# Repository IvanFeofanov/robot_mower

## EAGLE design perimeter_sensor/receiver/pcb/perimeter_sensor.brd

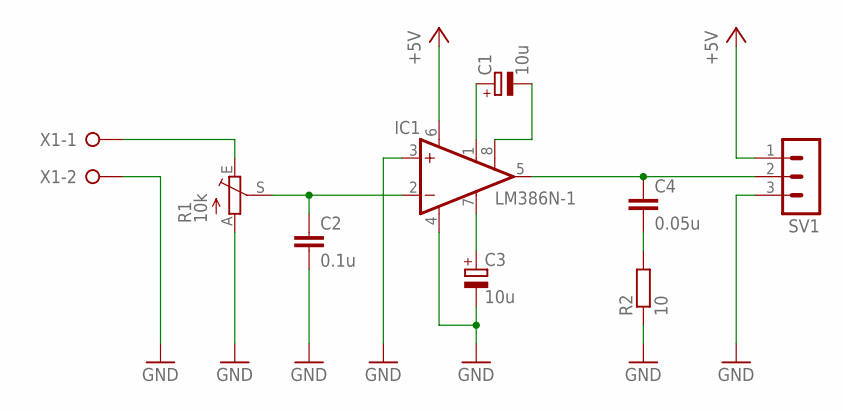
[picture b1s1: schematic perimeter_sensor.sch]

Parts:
C1, C3: 10u; E2,5-6
C2: 0.1u; C050-025X075
C4: 0.05u; C050-025X075
IC1: LM386N-1; DIL08
R1: 10k; S64W
R2: 10; 0204/7
SV1: MA03-1
X1: W237-02P; W237-132

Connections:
+5V: IC1.6 (VS), SV1.1
GND: C2.2, C3.-, IC1.3 (+IN), IC1.4 (GND), R1.A, R2.1, SV1.3, X1.2
unnamed: C1.-, IC1.8 (GAIN)
unnamed: C1.+, IC1.1 (GAIN)
unnamed: C3.+, IC1.7 (BYPASS)
unnamed: C2.1, IC1.2 (-IN), R1.S
unnamed: C4.1, IC1.5 (OUT), SV1.2
unnamed: C4.2, R2.2
unnamed: R1.E, X1.1

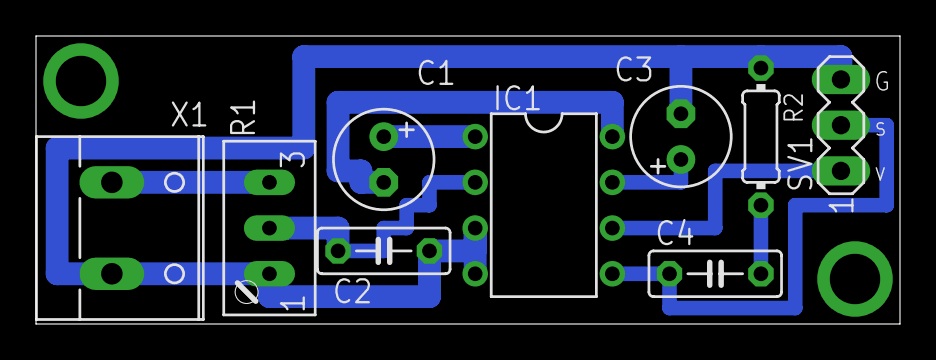
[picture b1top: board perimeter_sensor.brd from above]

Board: 2 copper layers, 48.0 x 16.0 mm, 9 parts (0 on the bottom side), 9 nets.

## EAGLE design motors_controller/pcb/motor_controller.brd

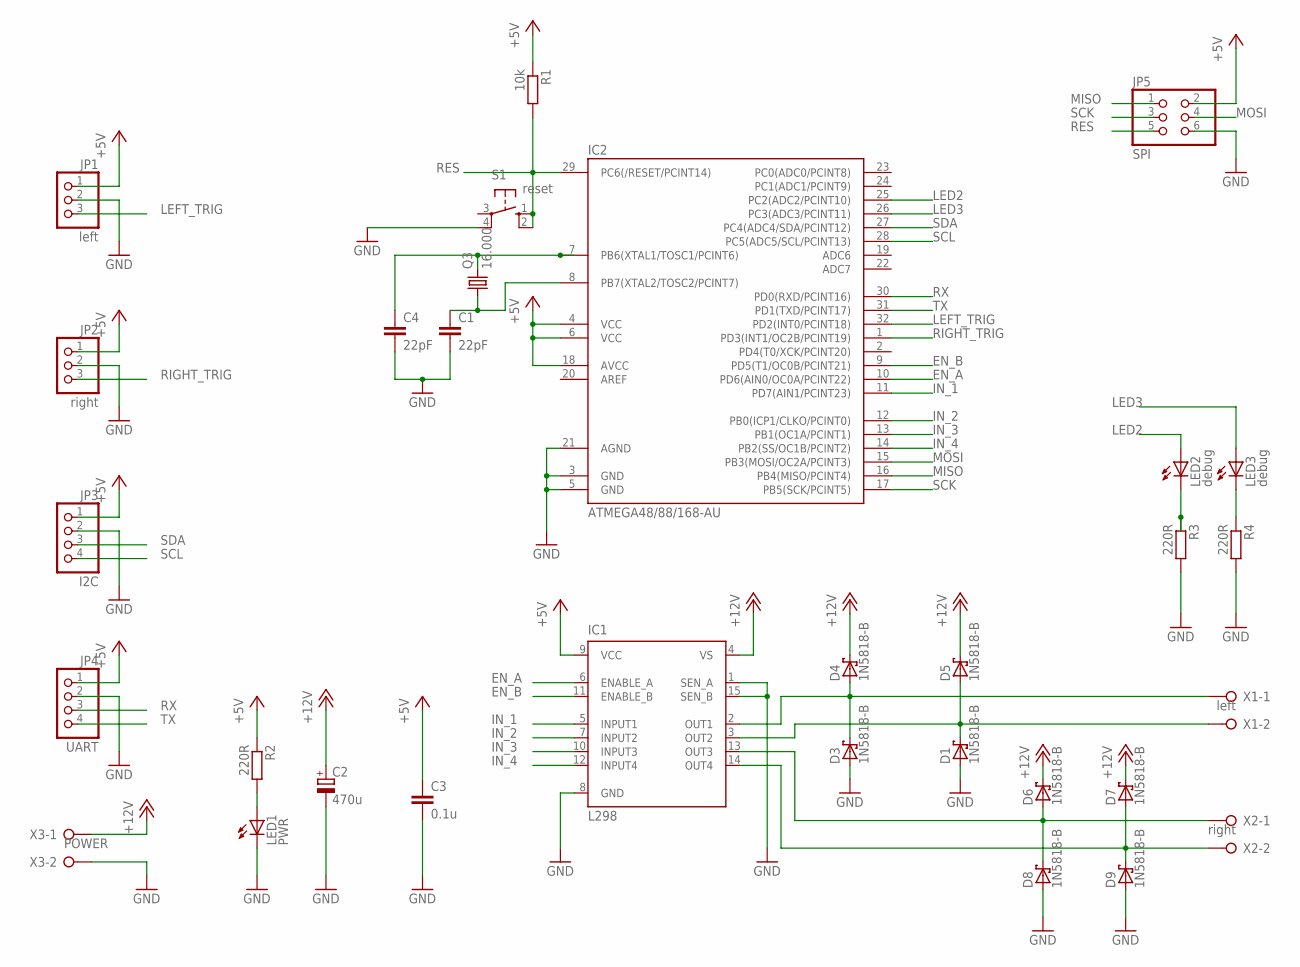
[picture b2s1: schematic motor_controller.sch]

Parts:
C1, C4: 22pF; C0805
C2: 470u; E5-10,5
C3: 0.1u; C0805
D1, D3, D4, D5, D6, D7, D8, D9: 1N5818-B; DO41-7.6
IC1: L298; MULTIWATT-15
IC2: ATMEGA48/88/168-AU; TQFP32-08
JP1: left; 1X03
JP2: right; 1X03
JP3: I2C; 1X04
JP4: UART; 1X04
JP5: SPI; 2X03
LED1: PWR; LED_1206
LED2, LED3: debug; LED_1206
Q3: 16.000; HC49UP
R1: 10k; R0805
R2, R3, R4: 220R; R0805
S1: reset; B3F-10XX
X1: left; W237-132
X2: right; W237-132
X3: POWER; W237-132

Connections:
+5V: C3.1, IC1.9 (VCC), IC2.4 (VCC), IC2.6 (VCC), IC2.18 (AVCC), JP1.1, JP2.1, JP3.1, JP4.1, JP5.2, R1.1, R2.1
+12V: C2.+, D4.C, D5.C, D6.C, D7.C, IC1.4 (VS), X3.1
EN_A: IC1.6 (ENABLE_A), IC2.10 (PD6(AIN0/OC0A/PCINT22))
EN_B: IC1.11 (ENABLE_B), IC2.9 (PD5(T1/OC0B/PCINT21))
GND: C1.2, C2.-, C3.2, C4.2, D1.A, D3.A, D8.A, D9.A, IC1.1 (SEN_A), IC1.8 (GND), IC1.15 (SEN_B), IC2.3 (GND), IC2.5 (GND), IC2.21 (AGND), JP1.2, JP2.2, JP3.2, JP4.2, JP5.6, LED1.C, R3.2, R4.2, S1.4 (P1), X3.2
IN_1: IC1.5 (INPUT1), IC2.11 (PD7(AIN1/PCINT23))
IN_2: IC1.7 (INPUT2), IC2.12 (PB0(ICP1/CLKO/PCINT0))
IN_3: IC1.10 (INPUT3), IC2.13 (PB1(OC1A/PCINT1))
IN_4: IC1.12 (INPUT4), IC2.14 (PB2(SS/OC1B/PCINT2))
LED2: IC2.25 (PC2(ADC2/PCINT10)), LED2.A
LED3: IC2.26 (PC3(ADC3/PCINT11)), LED3.A
LEFT_TRIG: IC2.32 (PD2(INT0/PCINT18)), JP1.3
MISO: IC2.16 (PB4(MISO/PCINT4)), JP5.1
MOSI: IC2.15 (PB3(MOSI/OC2A/PCINT3)), JP5.4
unnamed: LED1.A, R2.2
unnamed: C4.1, IC2.7 (PB6(XTAL1/TOSC1/PCINT6)), Q3.2
unnamed: C1.1, IC2.8 (PB7(XTAL2/TOSC2/PCINT7)), Q3.1
unnamed: LED3.C, R4.1
unnamed: LED2.C, R3.1
unnamed: D3.C, D4.A, IC1.2 (OUT1), X1.1
unnamed: D1.C, D5.A, IC1.3 (OUT2), X1.2
unnamed: D7.A, D9.C, IC1.14 (OUT4), X2.2
unnamed: D6.A, D8.C, IC1.13 (OUT3), X2.1
RES: IC2.29 (PC6(/RESET/PCINT14)), JP5.5, R1.2, S1.1 (S), S1.2 (S1)
RIGHT_TRIG: IC2.1 (PD3(INT1/OC2B/PCINT19)), JP2.3
RX: IC2.30 (PD0(RXD/PCINT16)), JP4.3
SCK: IC2.17 (PB5(SCK/PCINT5)), JP5.3
SCL: IC2.28 (PC5(ADC5/SCL/PCINT13)), JP3.4
SDA: IC2.27 (PC4(ADC4/SDA/PCINT12)), JP3.3
TX: IC2.31 (PD1(TXD/PCINT17)), JP4.4

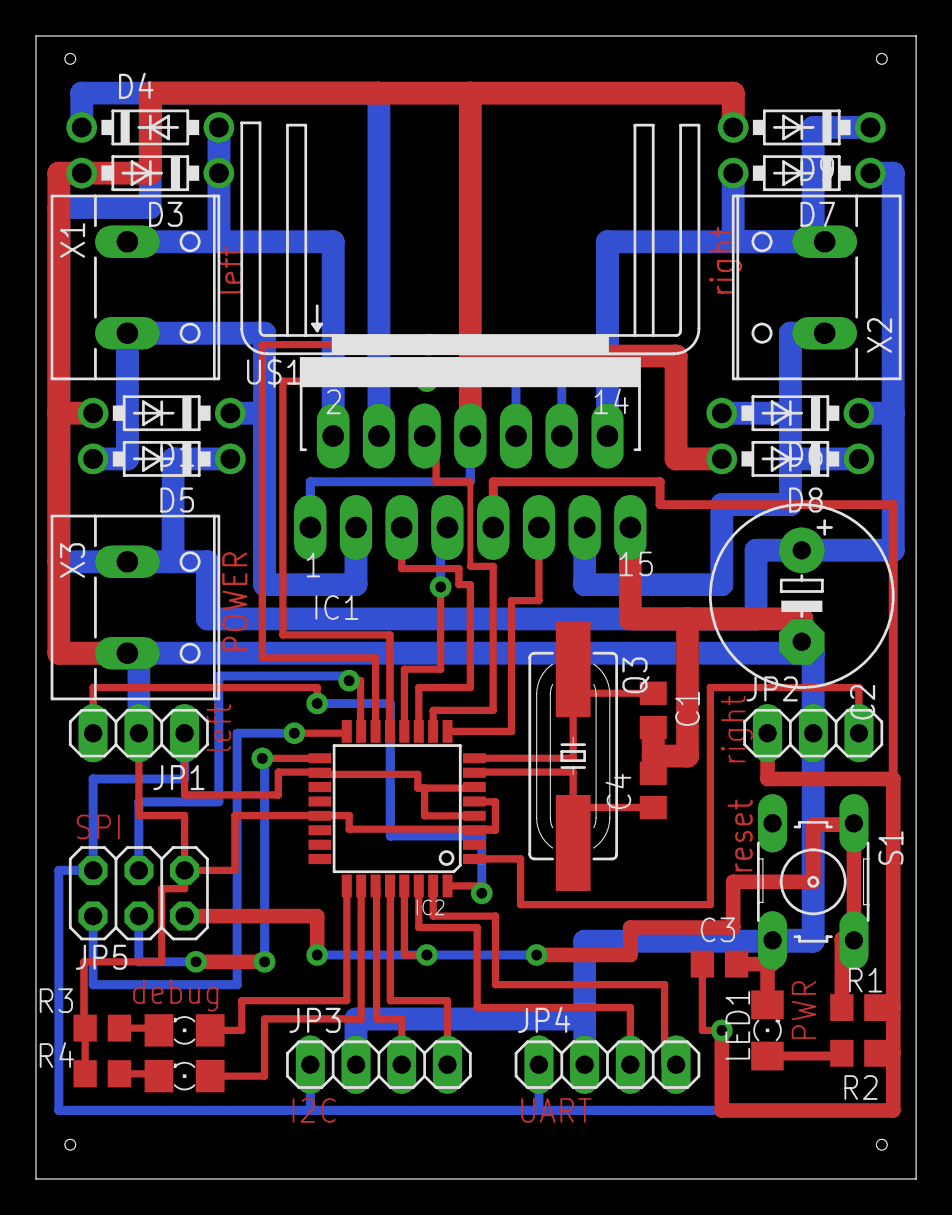
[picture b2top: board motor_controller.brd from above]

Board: 2 copper layers, 48.9 x 63.5 mm, 32 parts (0 on the bottom side), 30 nets.

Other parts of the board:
U$1: FK213

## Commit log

2016-11-20 init
2016-11-20 Added calculation of coil
2016-11-20 Added calculation of the current sensor
2016-11-26 Added current sensor program for microcontrollers
2016-12-04 Added module of odometers
2016-12-05 Added charging station scheme
2016-12-07 Added ring buffer class
2016-12-08 Added motor drive and terminal class
2016-12-09 Change schema of dock-station
2016-12-09 Added class of system timer
2016-12-11 Added class of pid regulator
2016-12-25 Added system of messages
2016-12-27 Rename gears.h to chassis.h
2016-12-27 Rename the fsm to the processes
2016-12-28 Added class of odometers
2016-12-28 New main loop
2016-12-28 added the PID controller configuration interface
2016-12-30 Rename drive_motor to the motor
2016-12-30 Rename chassis.h to motors_controller.h
2016-12-31 Added class of menu
2017-01-02 Added menu items
2017-01-03 Fixed pid regulator
2017-01-05 Deleted disable_interrupt.h
2017-01-12 init new branch
2017-01-13 Added driver of TWI
2017-01-18 Added class of twi slave
2017-01-18 Added class of twi interface
2017-01-19 Added saving system of PID controller settings
2017-01-20 Changed the way the sensors survey
2017-01-20 Added atmega88p hardware
2017-02-01 Added fuse bits for atmega88pa
2017-02-01 Fixed a bug int the PID
2017-02-07 added robot directory
2017-02-08 Добавлены средства индикации и контроля работы
2017-02-08 Добавлен блок управления двигателями косилки
2017-02-09 Добавлен модуль управления приводными двигателями
2017-02-12 Добавлен uart интерфей для контроля и отладки
2017-02-14 Добавлен код опроса бампера
2017-02-14 Renamed from odometers to motors_controller
2017-02-14 Added pcb for motors controller
2017-02-14 Added pcb for receiver of the perimeter sensor
2017-02-17 Добавлен код датчика периметра
2017-02-17 Added arduino-version of sender
2017-02-24 Добавилены данные тестов катушек для датчика периметра
2017-02-25 Исправлены ошибки в прошивке контроллера двигателей
2017-02-26 Добавлен алгоритм следования вдоль периметра
2017-03-28 Переделан алгоритм движения вдоль периметра.
2017-03-29 Переписаны автоматы бампера, индикатора и датчика периметра
2017-04-05 Переписан автомат косилки
2017-04-08 Добавлен шаблон автомата опроса тактовой кнопки
2017-04-23 Переделан автомат управление управления приводными двигателями
2017-05-06 Добавлено средство отладки
2017-07-23 Начал переделывать контроллер двигателей
2017-08-12 Добавлен SPI slave интерфейс
2017-08-12 -Удалили не используемые файлы twi интерфейса -Переделал контроллер двигателей
2017-08-17 Начал разработку SPI face
2017-08-19 Добавил драйвер SPI master
2017-08-20 Передалал DriveMotors под SPI интерфейс
2017-08-21 Доработал spi slave interface, освободил линию SS контроллера. Необходимо добавить новую схему платы двигателей и переделать ее разводку.
2017-08-22 Добавил контрольную сумму на передачу данных по SPI
2017-08-22 Исправлен баг в Flag
2017-08-23 Добавил контрольную сумму в MotorsController
2017-08-23 Перенес вывод управления на PIND3
2017-09-17 Сделал новый twi_face
2017-09-17 Заменил вывод управлени двигателем С5 на B2
2017-09-17 Удалил исходники spi интерфейса
2017-09-27 Новый Twi Master в главном контроллере
2017-09-30 Новый MotorsController
